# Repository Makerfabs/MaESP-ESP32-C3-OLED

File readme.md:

# MaESP ESP32 C3 OLED

```c++
/*
Version:		V1.2
Author:			Vincent
Create Date:	2022/9/23
Note:
	2022/12/30	V1.2: Change wiki link
	2022/10/26	V1.1: Add product link and wiki link
*/
```

[toc]

# Makerfabs

[Makerfabs home page](https://www.makerfabs.com/)

[Makerfabs Wiki](https://wiki.makerfabs.com/)

# MaESP ESP32 C3 OLED
## Intruduce

Product Link ： [MaESP ESP32-C3 Board with 1.3" OLED](https://www.makerfabs.com/maesp-esp32-c3-board-with-1-3-oled.html)

Wiki Link : [MaESP ESP32-C3 OLED](https://wiki.makerfabs.com/MaESP_ESP32_C3_OLED.html)

MaESP ESP32 C3 OLED equips with ESP32-C3, which is a single-core Wi-Fi and Bluetooth 5 (LE) microcontroller SoC, built around a 32-bit **RISC-V** chip processor with a four-stage pipeline that operates at up to 160 MHz, with 4MB Flash, 400KB SRAM. 

## Feature

- Controller: ESP32-C3-MINI-1-N4, 4MB Flash, RISCV-32bit, 160MHz, 400KB SRAM, Bluetooth 5
- Wireless: WiFi & Bluetooth 5.0
- Power Supply: USB Type-C 5.0V(4.0V~5.25V)
- Button: Flash button and reset button
- Arduino support: Yes
- Operation temperature: -40℃ to +85℃

# Code

## Complier Option

- Install board : ESP32 .
- Install library : Adafruit_SSD1306, Adafruit_GFX libraries. 
- Use type-c use cable connect USBto PC.
- Upload codes, select "ESP32-C3 DEV Module"
- Some times need press boot button and reset, when COM port not appear.

## Firmware

### CDC_OLED

Different from the commonly used Arduino, the USB interface is directly connected to the ESP32C3, without CP2104 and other chips.

 Therefore, to enable the serial port to send logs normally, use the USBSerial object. This demo show how to use USBSerial and show logo on OLED.

## Example

### NTP_Time

Need chang wifi config .

```c++
#define SSID "Makerfabs"
#define PWD "20160704"
```

Will display NTP time to OLED.

### DHT11_ThingSpeak

Need change ThingSpeak upload url to yourself.

```c++
    String url = "http://api.thingspeak.com/update?api_key=KCAT79TTH52MG7EA&field1=";
    url = url + t + "&field2=" + h;
```

It sends the current temperature and humidity to ThingSpeak when it starts up, and periodically displays the latest temperature and humidity to the OLED.

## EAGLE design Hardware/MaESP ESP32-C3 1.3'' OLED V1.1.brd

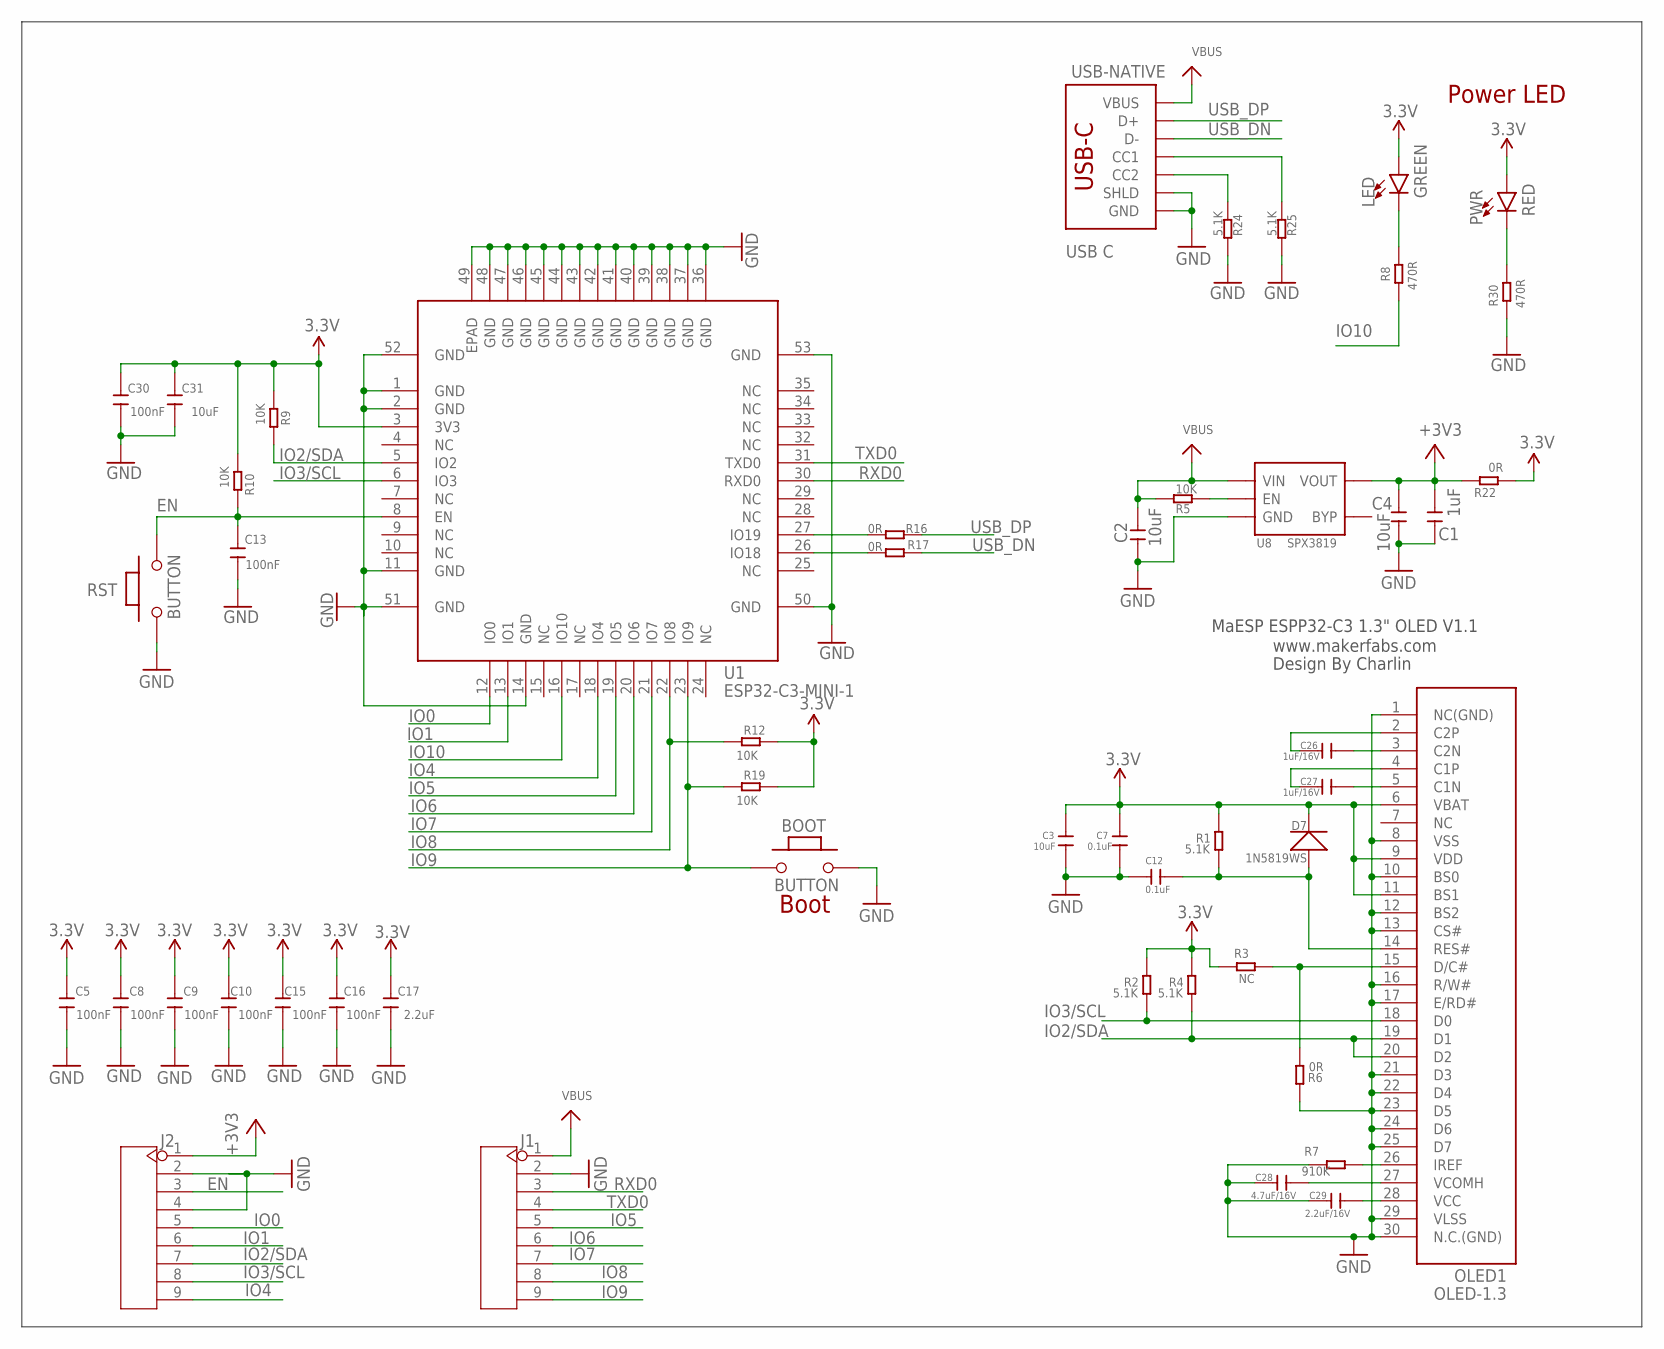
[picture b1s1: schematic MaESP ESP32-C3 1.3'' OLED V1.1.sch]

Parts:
BOOT: BUTTON; 157SW
C1: 1uF; C0603
C2, C3, C4, C31: 10uF; C0603
C5, C8, C9, C10, C13, C15, C16, C30: 100nF; C0603
C7, C12: 0.1uF; C0603
C17: 2.2uF; C0603
C26, C27: 1uF/16V; C0603
C28: 4.7uF/16V; C0603
C29: 2.2uF/16V; C0603
D7: 1N5819WS; SOD323
J1, J2: HEADER-9P-2.54; 9P-2.54
LED: GREEN; LED-0603
OLED1: OLED-1.3
PWR: RED; LED-0603
R1, R2, R4, R24, R25: 5.1K; R0603
R3: NC; R0603
R5, R9, R10, R12, R19: 10K; R0603
R6, R16, R17, R22: 0R; R0603
R7: 910K; R0603
R8, R30: 470R; R0603
RST: BUTTON; 157SW
U1: ESP32-C3-MINI-1
U8: SPX3819; SOT23-5
USB-NATIVE: USB C; USB-C-16P-4LAYER-ISOLATED

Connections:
3.3V: C3.1, C5.2, C7.1, C8.2, C9.2, C10.2, C15.2, C16.2, C17.2, C30.2, C31.2, D7.-, LED.A, OLED1.6 (VBAT), OLED1.9 (VDD), OLED1.11 (BS1), PWR.A, R1.2, R2.2, R3.2, R4.2, R9.1, R10.1, R12.2, R19.2, R22.1, U1.3 (3V3)
3V3_EN: R5.2, U8.3 (EN)
+3V3: C1.2, C4.2, J2.1, R22.2, U8.5 (VOUT)
EN: C13.2, J2.3, R10.2, RST.2, U1.8 (EN)
GND: BOOT.2, C1.1, C2.1, C3.2, C4.1, C5.1, C7.2, C8.1, C9.1, C10.1, C12.1, C13.1, C15.1, C16.1, C17.1, C28.1, C29.1, C30.1, C31.1, J1.2, J2.2, J2.4, OLED1.1 (NC(GND)), OLED1.8 (VSS), OLED1.10 (BS0), OLED1.12 (BS2), OLED1.13 (CS#), OLED1.16 (R/W#), OLED1.17 (E/RD#), OLED1.21 (D3), OLED1.22 (D4), OLED1.23 (D5), OLED1.24 (D6), OLED1.25 (D7), OLED1.29 (VLSS), OLED1.30 (N.C.(GND)), R6.2, R7.2, R24.1, R25.1, R30.2, RST.1, U1.1 (GND), U1.2 (GND), U1.11 (GND), U1.14 (GND), U1.36 (GND), U1.37 (GND), U1.38 (GND), U1.39 (GND), U1.40 (GND), U1.41 (GND), U1.42 (GND), U1.43 (GND), U1.44 (GND), U1.45 (GND), U1.46 (GND), U1.47 (GND), U1.48 (GND), U1.49 (EPAD), U1.50 (GND), U1.51 (GND), U1.52 (GND), U1.53 (GND), U8.2 (GND), USB-NATIVE.GND, USB-NATIVE.GND2 (GND), USB-NATIVE.SHLD1 (SHLD), USB-NATIVE.SHLD2 (SHLD), USB-NATIVE.SHLD3 (SHLD), USB-NATIVE.SHLD4 (SHLD), USB-NATIVE.SHLD5 (SHLD), USB-NATIVE.SHLD6 (SHLD), USB-NATIVE.SHLD7 (SHLD), USB-NATIVE.SHLD8 (SHLD)
IO0: J2.5, U1.12 (IO0)
IO1: J2.6, U1.13 (IO1)
IO2/SDA: J2.7, OLED1.19 (D1), OLED1.20 (D2), R4.1, R9.2, U1.5 (IO2)
IO3/SCL: J2.8, OLED1.18 (D0), R2.1, U1.6 (IO3)
IO4: J2.9, U1.18 (IO4)
IO5: J1.5, U1.19 (IO5)
IO6: J1.6, U1.20 (IO6)
IO7: J1.7, U1.21 (IO7)
IO8: J1.8, R12.1, U1.22 (IO8)
IO9: BOOT.1, J1.9, R19.1, U1.23 (IO9)
IO10: R8.2, U1.16 (IO10)
unnamed: LED.C, R8.1
unnamed: OLED1.15 (D/C#), R3.1, R6.1
unnamed: C28.2, OLED1.27 (VCOMH)
unnamed: PWR.C, R30.1
unnamed: C29.2, OLED1.28 (VCC)
unnamed: OLED1.26 (IREF), R7.1
unnamed: C26.2, OLED1.3 (C2N)
unnamed: R25.2, USB-NATIVE.A5 (CC1)
unnamed: R24.2, USB-NATIVE.B5 (CC2)
unnamed: C26.1, OLED1.2 (C2P)
unnamed: C27.1, OLED1.4 (C1P)
unnamed: C27.2, OLED1.5 (C1N)
unnamed: R17.1, U1.26 (IO18)
unnamed: R16.1, U1.27 (IO19)
unnamed: C12.2, D7.+, OLED1.14 (RES#), R1.1
RXD0: J1.3, U1.30 (RXD0)
TXD0: J1.4, U1.31 (TXD0)
USB_DN: R17.2, USB-NATIVE.A7 (D-), USB-NATIVE.B7 (D-)
USB_DP: R16.2, USB-NATIVE.A6 (D+), USB-NATIVE.B6 (D+)
VBUS: C2.2, J1.1, R5.1, U8.1 (VIN), USB-NATIVE.VBUS1 (VBUS), USB-NATIVE.VBUS2 (VBUS)

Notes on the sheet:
MaESP ESPP32-C3 1.3" OLED V1.1
www.makerfabs.com
Boot
Power LED
Design By Charlin

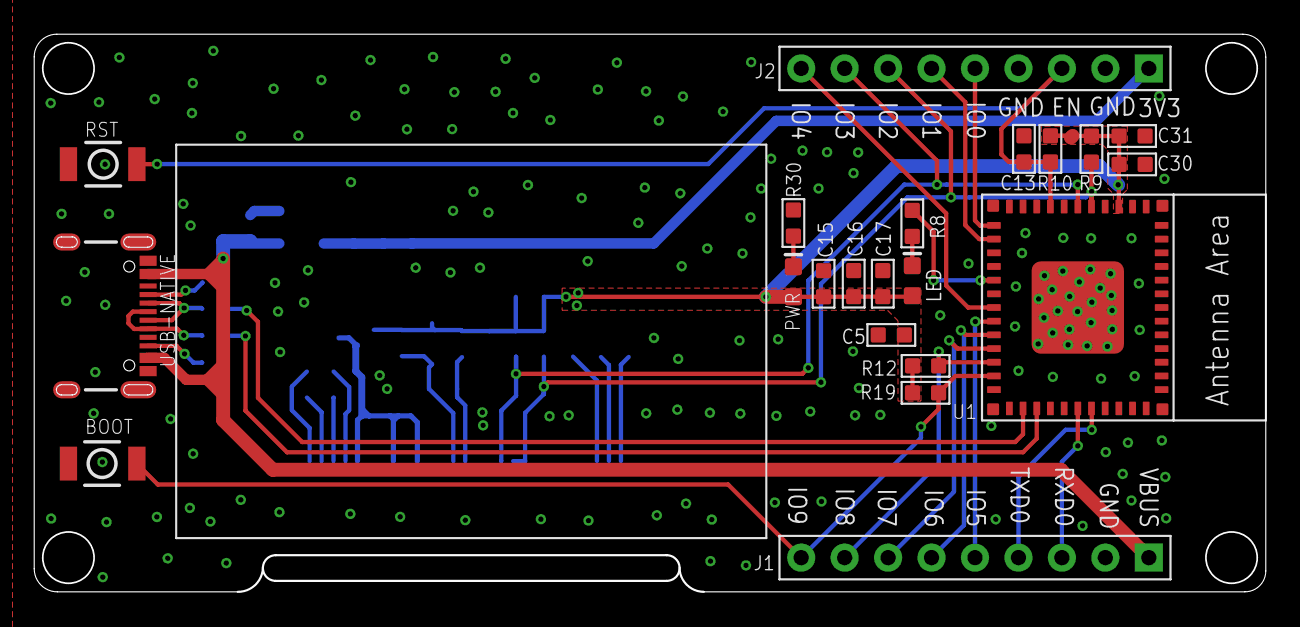
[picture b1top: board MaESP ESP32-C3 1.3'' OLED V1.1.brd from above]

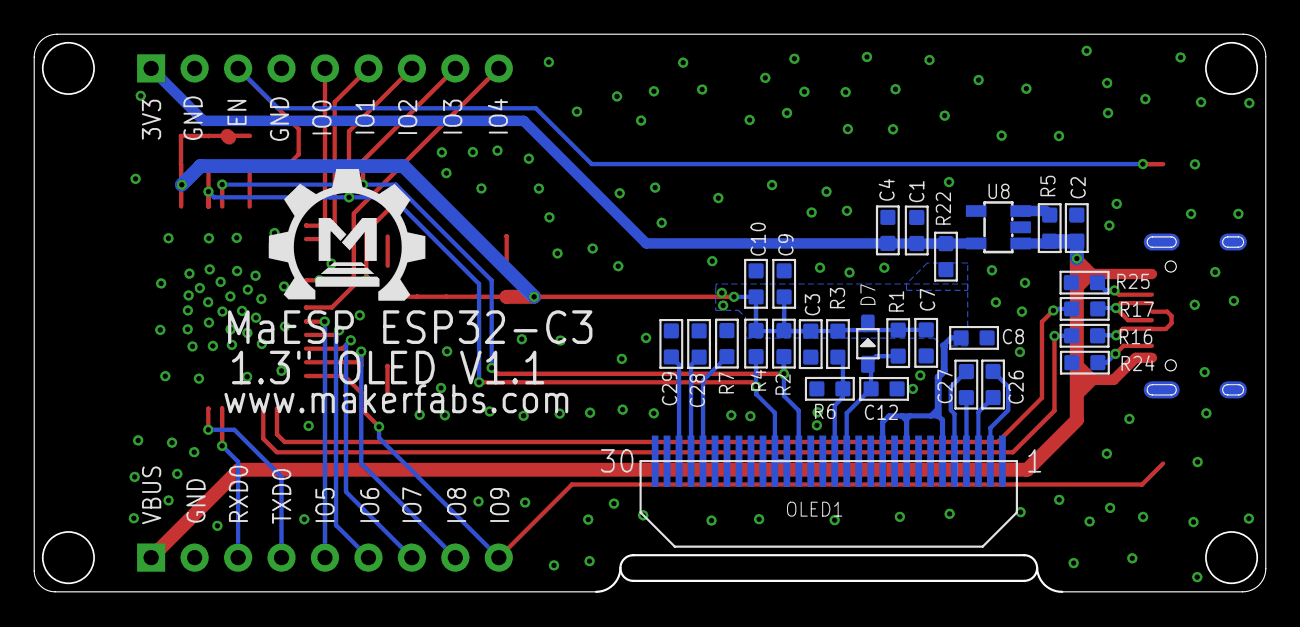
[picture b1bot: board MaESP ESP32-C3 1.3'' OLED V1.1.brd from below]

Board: 2 copper layers, 71.9 x 32.5 mm, 50 parts (28 on the bottom side), 36 nets.

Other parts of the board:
U$1: MAKERFABS_0.3

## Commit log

2022-10-13 Creart product
2022-10-15 Hardware
    v1.1
2022-10-15 Change example
2022-10-26 V1.1
2022-12-30 Edit readme

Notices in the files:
parts and their libraries:
SparkFun-Connectors: Licensing: Creative Commons ShareAlike 4.0 International - https://creativecommons.org/licenses/by-sa/4.0
microbuilder: This work is placed in the public domain, and may be freely used for commercial and non-commercial work with the following conditions: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
